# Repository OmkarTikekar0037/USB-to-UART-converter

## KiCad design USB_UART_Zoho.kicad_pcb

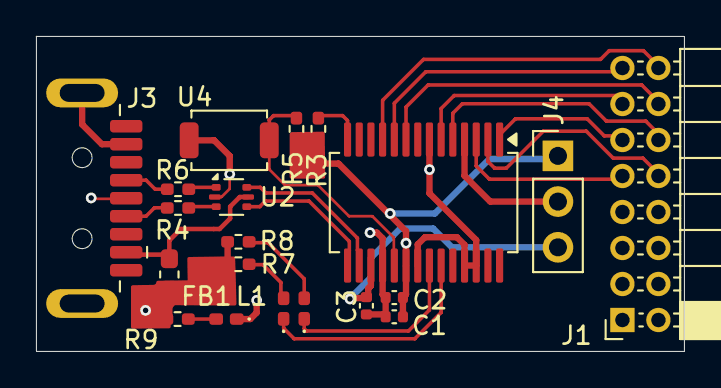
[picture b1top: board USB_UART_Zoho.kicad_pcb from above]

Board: 4 copper layers, 36.0 x 17.5 mm, 20 parts (0 on the bottom side), 18 nets.

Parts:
C1, C3: 100nF; C_0402_1005Metric
C2: 4.7uF; C_0402_1005Metric
FB1: FerriteBead; L_0603_1608Metric_Pad1.05x0.95mm_HandSolder
J1: Conn_02x08_Counter_Clockwise; PinSocket_2x08_P2.00mm_Horizontal
J3: USB3_A; USB3_A_Plug_Wuerth_692112030100_Horizontal
J4: VccIo_jumper; PinHeader_1x03_P2.54mm_Vertical
L1: LED; LED_0402_1005Metric_Pad0.77x0.64mm_HandSolder
R3: 10k; R_0402_1005Metric_Pad0.72x0.64mm_HandSolder
R4, R6: 27R; R_0402_1005Metric_Pad0.72x0.64mm_HandSolder
R5: 10K; R_0402_1005Metric_Pad0.72x0.64mm_HandSolder
R7, R8: 1k; R_0402_1005Metric_Pad0.72x0.64mm_HandSolder
R9: 1K; R_0402_1005Metric_Pad0.72x0.64mm_HandSolder
Rx_LED1: LED; LED_0402_1005Metric_Pad0.77x0.64mm_HandSolder
Tx_LED1: LED; LED_0402_1005Metric_Pad0.77x0.64mm_HandSolder
U1: FT232RL; SSOP-28_5.3x10.2mm_P0.65mm
U2: USBLC6-2P6; SOT-666
U4: SW_SPST_TS-1088-xR025

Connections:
3V3OUT: C3.1, J4.3, U1.17 (3V3OUT)
/D+: J3.3 (D+), R6.2
/D-: J3.2 (D-), R4.1
/RESET: R5.2, U1.19 (~RESET), U4.1
/Rx_LED: R8.2, Rx_LED1.2 (A)
/Tx_LED: R7.2, Tx_LED1.2 (A)
/d+: U1.15 (USBD+), U2.4 (I/O2)
/d-: U1.16 (USBD-), U2.6 (I/O1)
/d_N: R4.2, U2.3 (I/O2)
/d_P: R6.1, U2.1 (I/O1)
GND: C1.2, C2.2, C3.2, J3.4 (GND), J3.7 (DRAIN), J3.SH (SHIELD), L1.1 (K), U1.7 (GND), U1.18 (GND), U1.21 (GND), U1.25 (AGND), U1.26 (TEST), U2.2 (GND), U4.2
unnamed: L1.2 (A), R9.1
unnamed: Rx_LED1.1 (K), U1.22 (CBUS1)
unnamed: Tx_LED1.1 (K), U1.23 (CBUS0)
unnamed: R3.2, U1.14 (CBUS3)
VBUS: FB1.1, J3.1 (VBUS), U2.5 (VBUS)
VCC: C1.1, C2.1, FB1.2, J4.1, R3.1, R5.1, R7.1, R8.1, R9.2, U1.20 (VCC)
VCCIO: J4.2, U1.4 (VCCIO)

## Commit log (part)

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2026-06-07 improved design decisions from the previous layout
